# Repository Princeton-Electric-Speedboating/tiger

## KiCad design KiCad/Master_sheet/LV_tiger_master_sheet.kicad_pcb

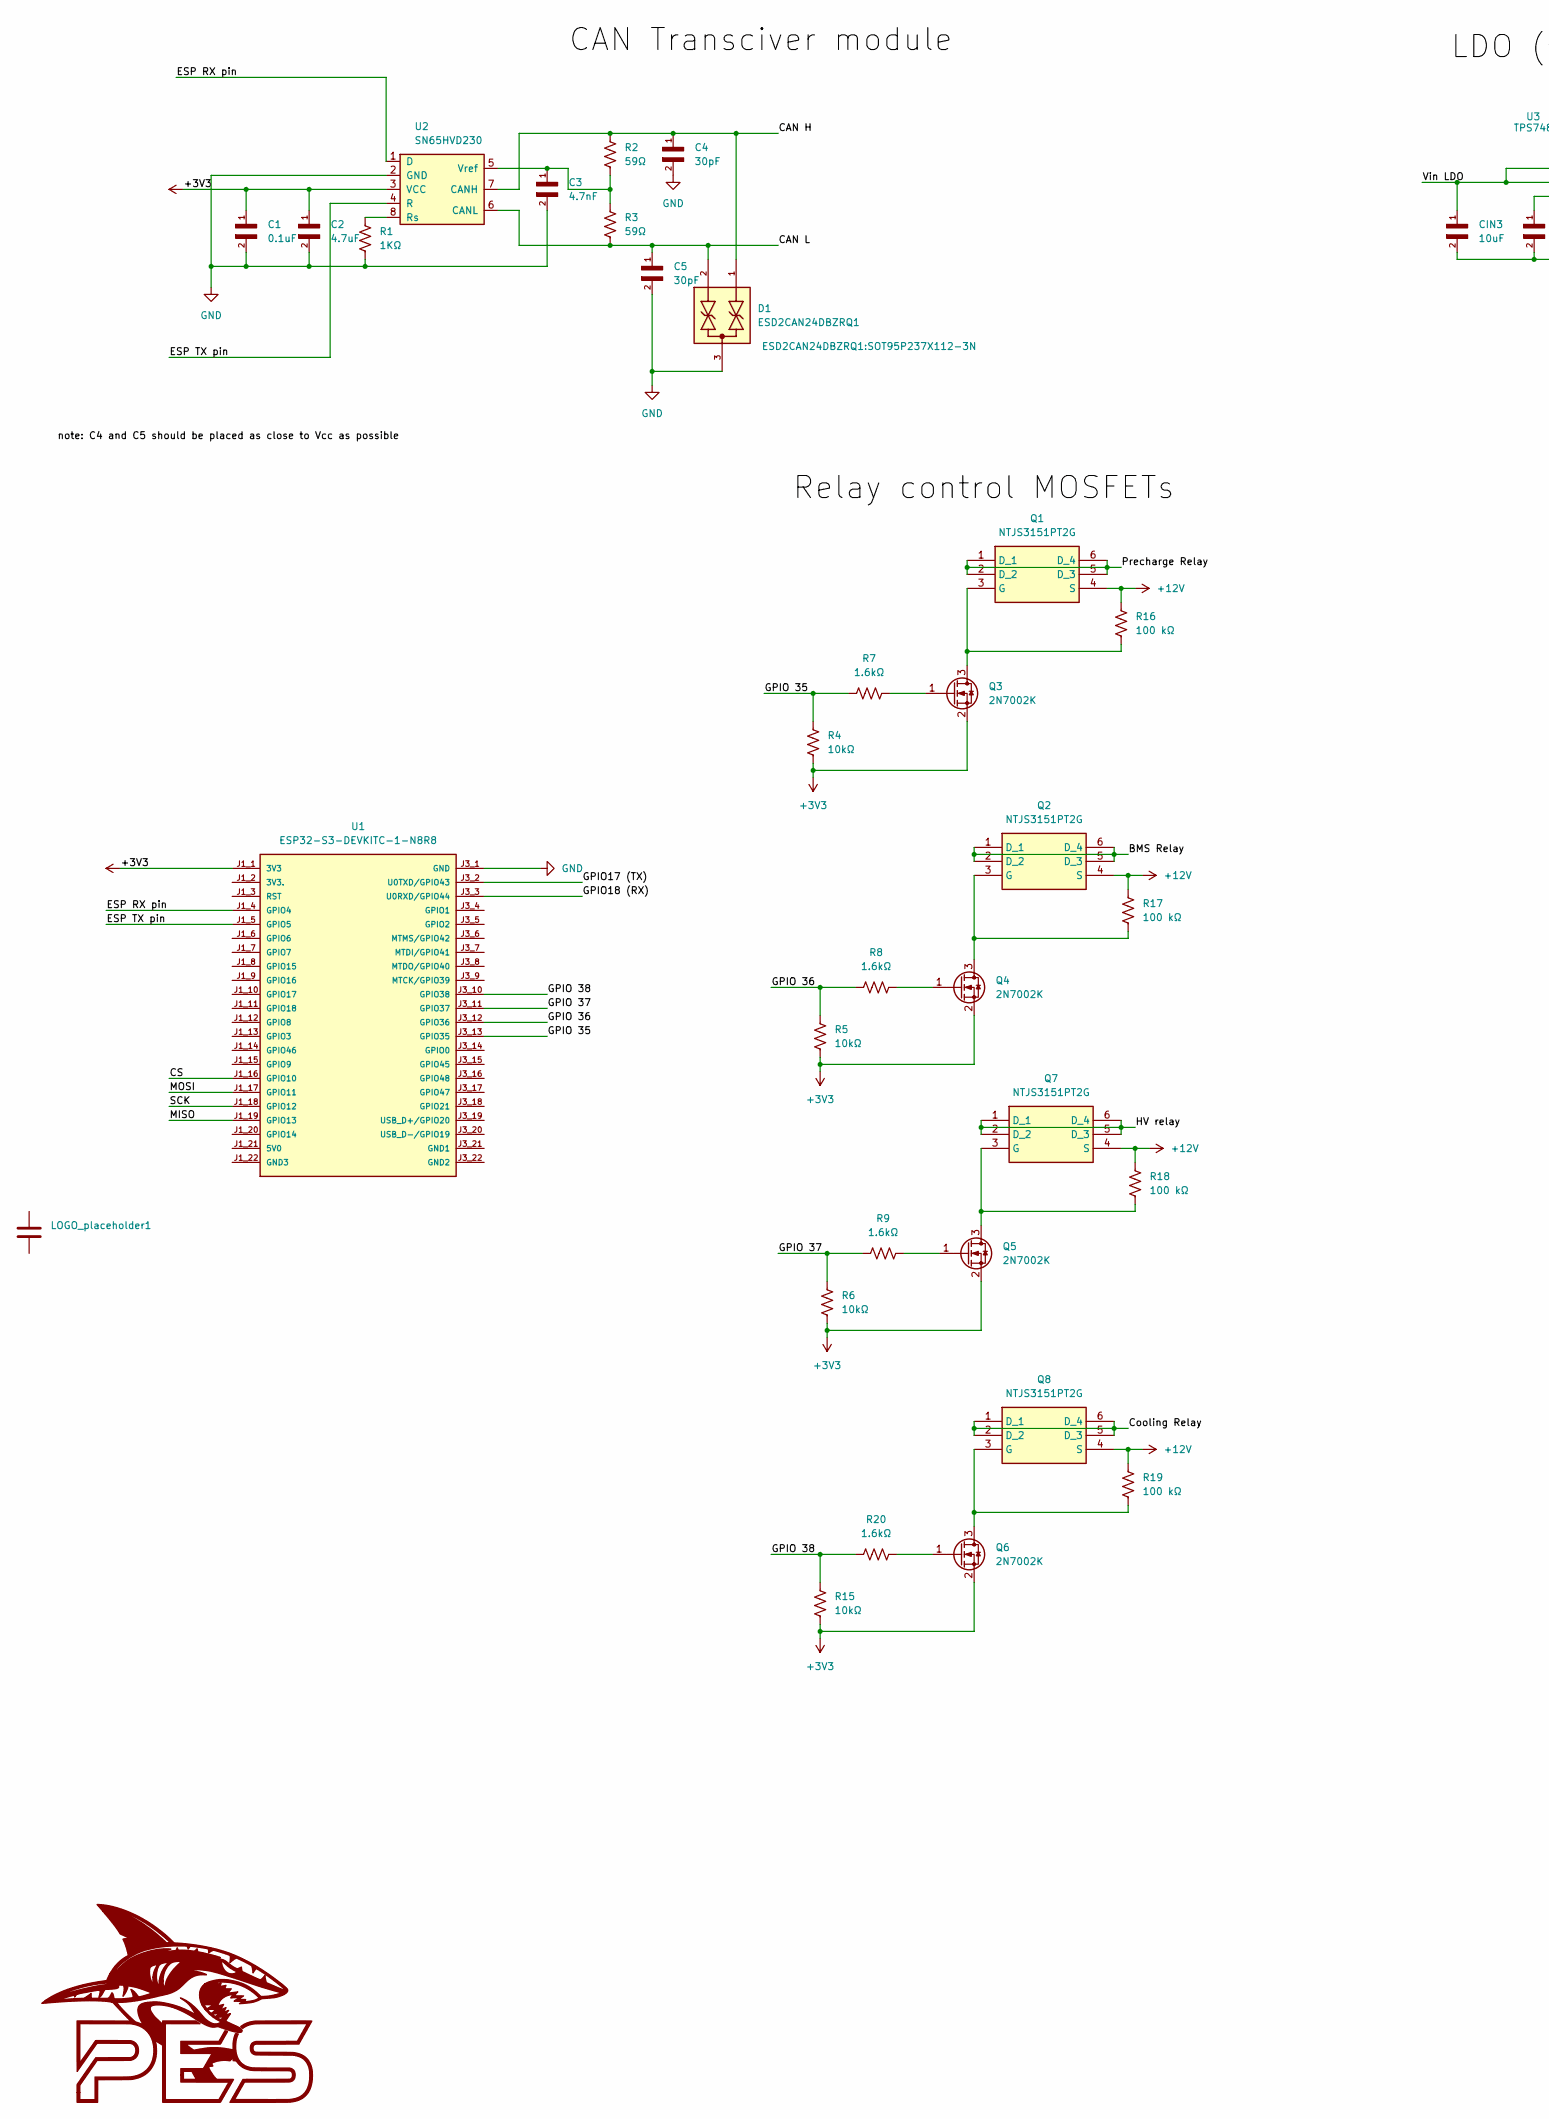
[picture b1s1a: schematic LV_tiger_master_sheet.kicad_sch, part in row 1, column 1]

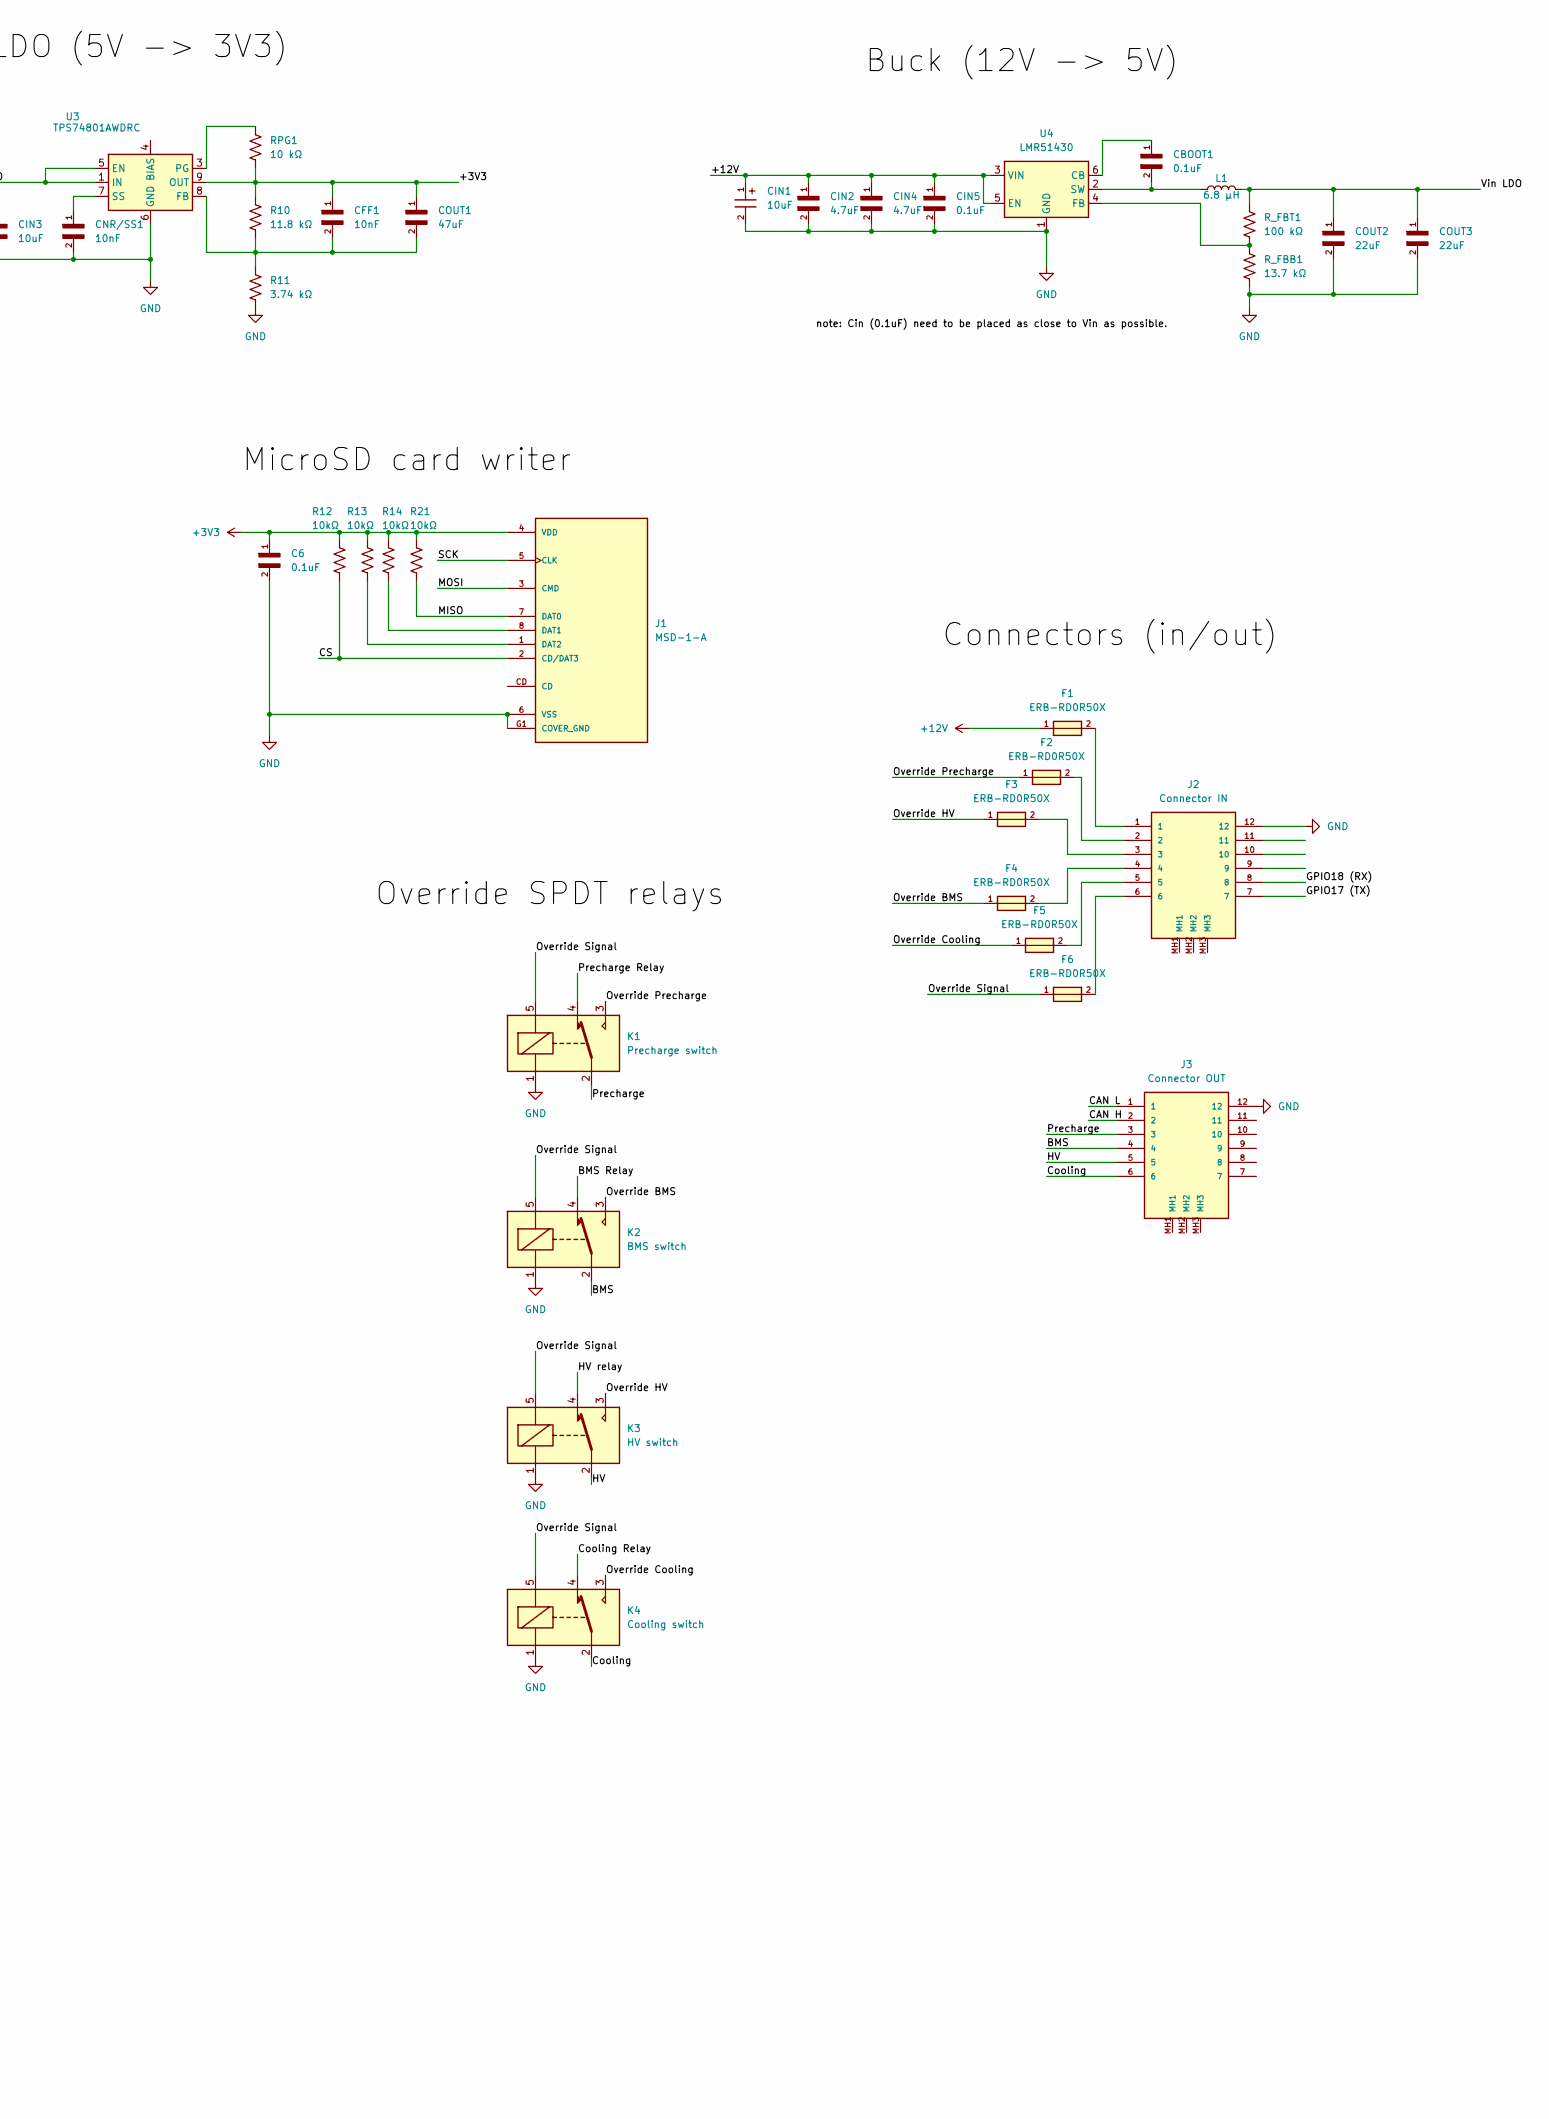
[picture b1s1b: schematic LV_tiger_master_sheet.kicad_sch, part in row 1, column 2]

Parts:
C1, C6: 0.1uF; CAPC1005X55N; DigiKey_Part_Number 1276-1043-1-ND
C2: 4.7uF; CAPC2012X140N
C3: 4.7nF; CAPC1005X55N
C4, C5: 30pF; CAPC0603X33N
CBOOT1: 0.1uF; CAPC1005X55N; DigiKey_Part_Number 1276-1043-1-ND
CFF1: 10nF; CAPC1005X55N
CIN1: 10uF; WCAP-ATG5_5X11_DXL_
CIN2, CIN4: 4.7uF; CAPC2012X140N
CIN3: 10uF; CAPC3216X180N
CIN5: 0.1uF; CAPC1005X55N; DigiKey_Part_Number 1276-1043-1-ND
CNR/SS1: 10nF; CAPC1005X55N
COUT1: 47uF; CAPC2012X145N
COUT2, COUT3: 22uF; CAPC2012X145N
D1: ESD2CAN24DBZRQ1; SOT95P237X112-3N; PARTREV C
F1, F2, F3, F4, F5, F6: ERB-RD0R50X; FUSC0402X49N
J1: MSD-1-A; CUI_MSD-1-A; PARTREV 1.0
J2: Connector IN; DT13-12
J3: Connector OUT; DT13-12
K1: Precharge switch; Relay_SPDT_Omron-G5Q-1
K2: BMS switch; Relay_SPDT_Omron-G5Q-1
K3: HV switch; Relay_SPDT_Omron-G5Q-1
K4: Cooling switch; Relay_SPDT_Omron-G5Q-1
L1: 6.8 µH; IND_VLS6045EX-6R8M
LOGO_placeholder1: C; new_pes_logo
Q1, Q2, Q7, Q8: NTJS3151PT2G; SOT65P210X110-6N; Mouser Part Number 863-NTJS3151PT2G
Q3, Q4, Q5, Q6: 2N7002K; SOT-23
R1: 1KΩ; RESC1508X55N
R2, R3: 59Ω; R_0201_0603Metric_Pad0.64x0.40mm_HandSolder
R4, R5, R6, R12, R13, R14, R15, R21: 10kΩ; RESC1607X60N
R7, R8, R9, R20: 1.6kΩ; RESC3116X65N
R10: 11.8 kΩ; RESC1005X40N
R11: 3.74 kΩ; RESC0603X26N
R16, R17, R18, R19: 100 kΩ; RESC1005X40
RPG1: 10 kΩ; RESC1607X60N
R_FBB1: 13.7 kΩ; RESC1005X40N
R_FBT1: 100 kΩ; RESC1005X40
U1: ESP32-S3-DEVKITC-1-N8R8
U2: SN65HVD230; SOIC-8_3.9x4.9mm_P1.27mm
U3: TPS74801AWDRC; VSON-10-1EP_3x3mm_P0.5mm_EP1.65x2.4mm_ThermalVias
U4: LMR51430; SOT-23-6

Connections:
+3V3: C1.1, C2.1, C6.1, CFF1.1, COUT1.1, J1.4 (VDD), Q3.2 (S), Q4.2 (S), Q5.2 (S), Q6.2 (S), R4.2, R5.2, R6.2, R10.1, R12.1, R13.1, R14.1, R15.2, R21.1, RPG1.2, U1.J1_1 (3V3), U2.3 (VCC), U3.9 (OUT)
+12V: CIN1.1, CIN2.1, CIN4.1, CIN5.1, F1.1, Q1.4 (S), Q2.4 (S), Q7.4 (S), Q8.4 (S), R16.1, R17.1, R18.1, R19.1, U4.3 (VIN), U4.5 (EN)
/BMS: J3.4, K2.2
/BMS Relay: K2.4, Q2.1 (D_1), Q2.2 (D_2), Q2.5 (D_3), Q2.6 (D_4)
/CAN H: C4.1, D1.1, J3.2, R2.1, U2.7 (CANH)
/CAN L: C5.1, D1.2, J3.1, R3.2, U2.6 (CANL)
/CS: J1.2 (CD/DAT3), R12.2, U1.J1_16 (GPIO10)
/Cooling: J3.6, K4.2
/Cooling Relay: K4.4, Q8.1 (D_1), Q8.2 (D_2), Q8.5 (D_3), Q8.6 (D_4)
/ESP RX pin: U1.J1_4 (GPIO4), U2.1 (D)
/ESP TX pin: U1.J1_5 (GPIO5), U2.4 (R)
/GPIO17 (TX): J2.7, U1.J3_2 (U0TXD/GPIO43)
/GPIO18 (RX): J2.8, U1.J3_3 (U0RXD/GPIO44)
/GPIO 35: R4.1, R7.2, U1.J3_13 (GPIO35)
/GPIO 36: R5.1, R8.2, U1.J3_12 (GPIO36)
/GPIO 37: R6.1, R9.2, U1.J3_11 (GPIO37)
/GPIO 38: R15.1, R20.2, U1.J3_10 (GPIO38)
/HV: J3.5, K3.2
/HV relay: K3.4, Q7.1 (D_1), Q7.2 (D_2), Q7.5 (D_3), Q7.6 (D_4)
/MISO: J1.7 (DAT0), R21.2, U1.J1_19 (GPIO13)
/MOSI: J1.3 (CMD), U1.J1_17 (GPIO11)
/Override BMS: F4.1, K2.3
/Override Cooling: F5.1, K4.3
/Override HV: F3.1, K3.3
/Override Precharge: F2.1, K1.3
/Override Signal: F6.1, K1.5, K2.5, K3.5, K4.5
/Precharge: J3.3, K1.2
/Precharge Relay: K1.4, Q1.1 (D_1), Q1.2 (D_2), Q1.5 (D_3), Q1.6 (D_4)
/SCK: J1.5 (CLK), U1.J1_18 (GPIO12)
/Vin LDO: CIN3.1, COUT2.1, COUT3.1, L1.2, R_FBT1.1, U3.1 (IN), U3.2 (IN), U3.5 (EN)
GND: C1.2, C2.2, C3.2, C4.2, C5.2, C6.2, CIN1.2, CIN2.2, CIN3.2, CIN4.2, CIN5.2, CNR/SS1.2, COUT2.2, COUT3.2, D1.3, J1.6 (VSS), J1.G1 (COVER_GND), J1.G2 (COVER_GND), J1.G3 (COVER_GND), J1.G4 (COVER_GND), J2.12, J3.12, K1.1, K2.1, K3.1, K4.1, R1.2, R11.2, R_FBB1.2, U1.J3_1 (GND), U2.2 (GND), U3.6 (GND), U3.11 (GND), U4.1 (GND)
unnamed: F1.2, J2.1
unnamed: F2.2, J2.2
unnamed: F3.2, J2.3
unnamed: F4.2, J2.4
unnamed: F5.2, J2.5
unnamed: F6.2, J2.6
unnamed: J1.8 (DAT1), R14.2
unnamed: J1.1 (DAT2), R13.2
unnamed: Q1.3 (G), Q3.3 (D), R16.2
unnamed: Q2.3 (G), Q4.3 (D), R17.2
unnamed: Q3.1 (G), R7.1
unnamed: Q4.1 (G), R8.1
unnamed: Q5.3 (D), Q7.3 (G), R18.2
unnamed: Q5.1 (G), R9.1
unnamed: Q6.3 (D), Q8.3 (G), R19.2
unnamed: Q6.1 (G), R20.1
unnamed: R1.1, U2.8 (Rs)
unnamed: C3.1, R2.2, R3.1, U2.5 (Vref)
unnamed: CFF1.2, COUT1.2, R10.2, R11.1, U3.8 (FB)
unnamed: RPG1.1, U3.3 (PG), U3.10 (OUT)
unnamed: CNR/SS1.1, U3.7 (SS)
unnamed: CBOOT1.1, U4.6 (CB)
unnamed: R_FBB1.1, R_FBT1.2, U4.4 (FB)
unnamed: CBOOT1.2, L1.1, U4.2 (SW)

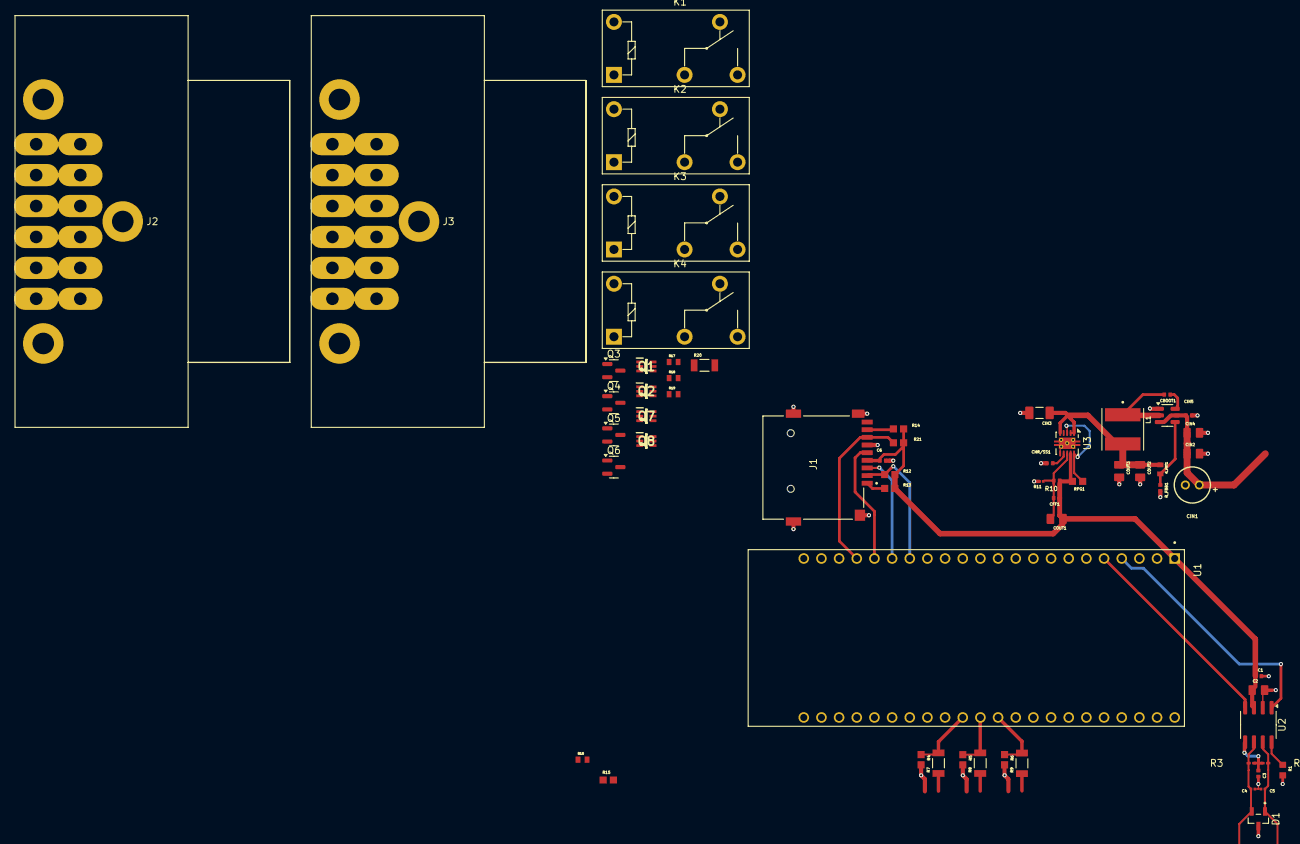
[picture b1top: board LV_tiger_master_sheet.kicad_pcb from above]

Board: 2 copper layers, 63 parts (0 on the bottom side), 45 nets.

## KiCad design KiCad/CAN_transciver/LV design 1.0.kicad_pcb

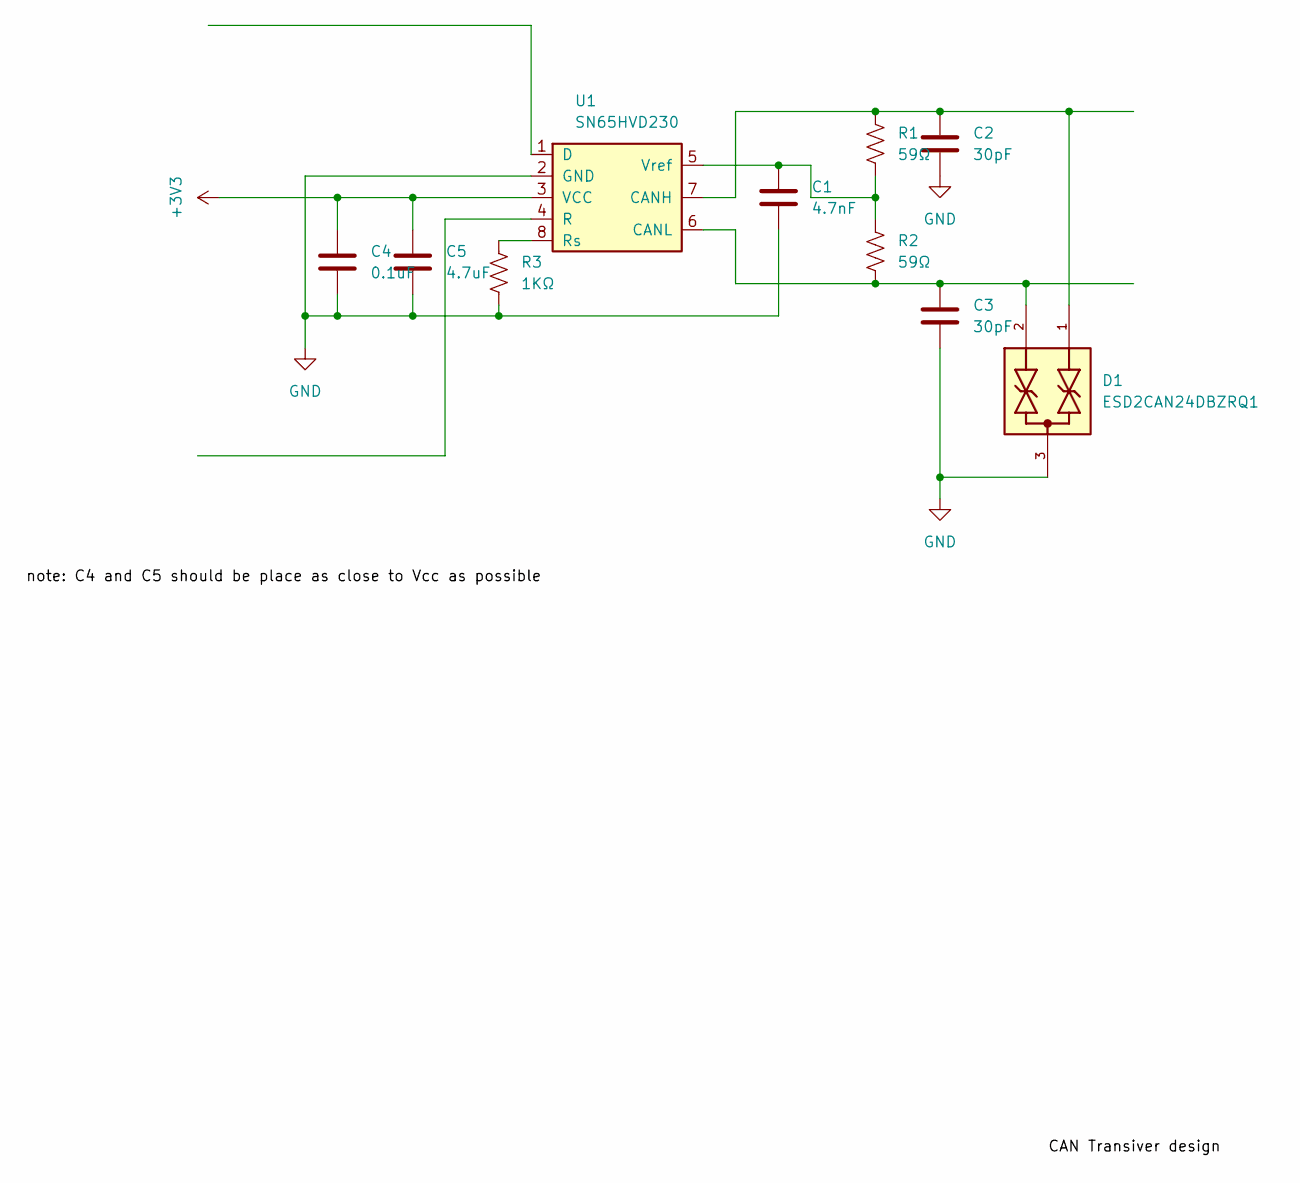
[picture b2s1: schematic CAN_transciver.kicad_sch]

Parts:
C1: 4.7nF
C2, C3: 30pF
C4: 0.1uF
C5: 4.7uF
D1: ESD2CAN24DBZRQ1; SOT95P237X112-3N; PARTREV C
R1, R2: 59Ω
R3: 1KΩ
U1: SN65HVD230; SOIC-8_3.9x4.9mm_P1.27mm

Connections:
+3V3: C4.1, C5.1, U1.3 (VCC)
GND: C1.2, C2.2, C3.2, C4.2, C5.2, D1.3, R3.2, U1.2 (GND)
unnamed: C2.1, D1.1, R1.1, U1.7 (CANH)
unnamed: C3.1, D1.2, R2.2, U1.6 (CANL)
unnamed: R3.1, U1.8 (Rs)
unnamed: C1.1, R1.2, R2.1, U1.5 (Vref)

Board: 2 copper layers, 10 parts (0 on the bottom side), 6 nets, no tracks yet.

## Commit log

2025-11-05 Skeleton
2025-11-08 added PCB schematic for CAN Tranciver
2025-11-08 added can transciver schematic
2025-11-08 Prototype CAN processor
2025-11-09 added rest of can ts files
2025-11-17 added master shcematic for LV PCB
2025-11-29 finished PCB
2025-12-01 made some changes to pcb layout
2025-12-21 added SD card write code (not connected with CAN yet)
2025-12-26 New VCU project setup with initial tasks and configurations
2025-12-28 made a lot of revisions to the schematic, not yet updated pcb layout
2025-12-28 made schematic look cleaner
